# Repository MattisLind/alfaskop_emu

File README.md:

# Alfaskop project

This project aims to make a Alfaskop 4110 running towards the Hercules IBM mainframe emulator and run the Memo mail software by [Verimation](http://www.verimation.se/).

## Alfaskop

The Alfaskop terminal was a big success for the early Swedish IT industry. The product was originally developed by SRT, Standard Radio & Telefon AB which was an ITT owned company. Later the Alfaskop part was moved in to the partly state owned Stansaab. Which then became DataSAAB. DataSAAB was bought by Ericsson to be part of the EIS business unit. Later on when Ericsson concetrated resources on telecom the EIS unit was sold to Nokia. Eventually Nokia part became ICL and the terminal division ended up in terminal manufacturer Wyse Technologies. 

In total 900 000 units were delivered world wide.
More information about the Alfaskop Series 41, marketing material and technical documents can be found [here.](http://www.datormuseum.se/peripherals/terminals/alfaskop). The development of the Alfaskop series of terminals started in the late 1960ies. The first displays, 3100, emulated the IBM 2260 series of terminals. Later models 3500 and 3700 emulated the IBM 3275 and IBM 3277 terminals. S/41 (4100) series emulated te IBM 3278 and IBM 3279 terminals. The S/41 series evolved in into the S/91 seires, with similar capabilities as the S/41 but in more modern hardware.

## Memo mail

The Memo software was originally developed by Volvo IT in the late 1970ies. At its [peak in 1992 over 800](https://sv.wikipedia.org/wiki/Memo_Mail) of the largest coporations in the world used Memo Mail. Memo mail is still developed and maintained by [Verimation AB](http://www.verimation.se/). A [text](https://www.diva-portal.org/smash/get/diva2:80406/FULLTEXT01.pdf) on Memo mail and other early mail systems developed.

## Hercules

The [Hercules](http://www.hercules-390.org/) project aims at emulating the IBM mainframes with its roots in the IBM S/360 architecture. This architecture has seens extensive development since the mid 1960ies when it was introduced. First by the S/370 series and then onto today with the z-series.

## Why
There are today not one single Alfaskop Series 41 terminal that is able to run and show what is was like. The root cause
is that the system as a whole was quite complex. The system 41 terminal of Display Unit (DU) requires a communication processor and a floppy drive (FD) to be able to run. It also has no software built in but loads this from the cluster.
Interfacing towards the cluster is quite complex. It uses synchronous communication and requires specialized hardware to communicate. All these factors jointly most likely made most of these units end up in the trash rather than saved.

Since the system has had an important role in the Swedish IT industry it would be very intersting to show how this system could operate in reality. We wanted to preserve an operating ALfaskop system and demonstrate it operating with as high fidelity as possible.

## Architecture

The above picture show the overall system architecture. It involves tha full Alfaskop cluster with floppy unit and cluster controller together with the terminal itself. The cluster connects using synchronous BSC communication. A small STM32 microcontroller takes care of the BSC protocol. It handles the byte synchronization and the CRC generation and checking. The data is then sent over a ordinary asnynchronous serial line to the Raspberyy Pi serial port. Inside the Raspberry Pi the socat software takes the data from the serial ports and redirects it to the BSC/TCP port of Hercules. Inside Hercules there is an emulation for the IBM 2703 communication unit. The 2703 is controlled by the TCAM software of the MVS operating system. On top of TCAM the TSO, Time Sharing Option, is running which allow users to log in to the system.

## 3270 Data Stream and IBM BSC protocol

The Alfaskop terminals were mostly used for emulating the IBM 3270 terminal series. Although other emulations were available. The software provided from DDHF is the 3270 BSC variant. The 3270 data stream is described in [this](http://bitsavers.trailing-edge.com/pdf/ibm/3270/GA23-0059-4_3270_Data_Stream_Programmers_Reference_Dec88.pdf) document. The [documentatation](http://bitsavers.org/pdf/ibm/3274/GA23-0061-1_3274_Control_Unit_Description_and_Programmers_Guide_Jan84.pdf) for the IBM 3274 Control Unit provide relevant information on how the communication towards the host takes place. The communicationprocessor could either be connected locally to the IBM main frame or remotely using a dial-up or leased line. In the host end there is a [2703](http://bitsavers.informatik.uni-stuttgart.de/pdf/ibm/2703/GA27-2703-1_2703_Transmission_Ctl_Component_Descr_May67.pdf) or [3704](http://bitsavers.informatik.uni-stuttgart.de/pdf/ibm/3704_3705/GC30-3004-5_3704_3705_Communications_Controller_Principles_of_Operation_May1979.pdf) or similar IBM communication unit that interfaces towards the IBM processor. The line normally used 9600 bps syncrounous BSC communication described in [this](http://bitsavers.trailing-edge.com/pdf/ibm/datacomm/GA27-3004-2_General_Information_Binary_Synchronous_Communications_Oct70.pdf) document.

## Alfaskop software

The Alfaskop Series 41 was primarily used as a terminal with emulating various terminal types, like IBM 3278, UNIVAC UTS 400, DEC VT100 etc. The Alfaskop series of terminals were programmed in a special language, SPL. From the beginning this meant StanSAAB Programming Language and was a modified variant of PL/1 programming language. The SPL programming language was developed in PL/1 on a IBM mainframe by a consultant that worked for Stansaab as an under consultant for Programmator around 1977-1978. He worked closely with the person developing the operating system. The operating system was coded entirely in 6800 assembler. The SPL programming language allowed inline assembler constructs if the software developer wanted to improve performance and the compiler has mechanims to do optimizations on the global level.

Later on other software was developed for the Alfaskop series 41, like Alfaword, which was a wordprocessing package.  Another package was called Alfaform. These software packages were also coded in the SPL programming language. There was also a port of the UCSD p-system to the System 41 series. Together with FD4120 floppy drive a complete personal computer was formed. The only software found this far is the 3278 terminal emulation software to be used in the clustered configuraration (4016). Unfortunately very little software for the Alfaskop system has been preserved. If you happen to have any software for the Alfaskop series, please get in contact with me. 

The system software diskette 4016 has been found at Dansk Datahistorisk Förening. This disk has origninally been with SAS. People at DDHF made an image dump of this disk and provided it to us.

## Old architecture idea

In the beginning of this project we had no access to a CPR4101 neither a FD4120 unit. The initial idea was that based on the software  and the scematics that was available an emulation of the floppy unit and cluster controller could be developed in the MAME framework. It turned out to be quite complicated and is still unfinished. The lack of specification of the programmable logic parts turned out to be a major problem since large part of the interrupt handling was taking place in them. When we eventually were able to get our hands on the real units the focus shited to get the full system running and not emulating parts of the cluster. Thus this the old architecture that was envisioned.

The basic idea is to use MAME to emulate the CP and the FD. All technical documentation and schematics are available and is scanned.

To communicate between the various entities of the cluster a TCP variant of the two wire bus will be created eumlating the 32 ports of the CP. To interface to the real Alfaskop DU 4110 a two-wire bus to TCP bridge will be created. In the first implementation it will use an Ericsson TWIB PC board connected to a small uController and a ESP32. Later on the interfacing will be done using a CPLD connected to a ESP32. The CPLD will handle HDLC and include the MODEM.

## Interfacing with SS3

The special twinax connnector used for the Alfaskop series was devolped by Ossi Carlsson AB, an ELDON AB company. The bus called SS3 which employed a 9.585 MHz (half the pixel clock of the terminal) clock to recover the approximately 300 kbit/s signal modulated by FFSK. The signalling over the link employed HDLC. Initially the FFSK modem was implemented using discrete TTL circuits and a bipolar PROM. Later on a Ferranti ULA (custom IC) was designed which did the entire modulation and demodulation process. 

In an attempt to interface to the SS3 bus the easiest was to actually reuse one of the Ericsson made TWIB PC-bus boards that happened to be available. The board is very simple and has just the Intel 8274 HDLC chip and some adress decoding as well as DMA and interrupt logic. Apart for that there is also a twin wire MODEM circuitry including the Ferranti ULA.

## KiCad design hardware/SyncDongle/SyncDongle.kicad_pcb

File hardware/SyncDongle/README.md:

# SyncDongle

SyncDongle is a STM32F103 BluePill or STM32F4x1 Weact blackpill board that interfaces to a sync port. It has the STM32 CPU card and a couple of MAX208 RS-232 level converters, a DB25 connector, a DE9 connector and 10 pin DIP switch / wire wrap area to set various configurations of the serial port. At this point the firmware available only support the STM32F103 BluePill. Support for the Weact black pill will be added later on.

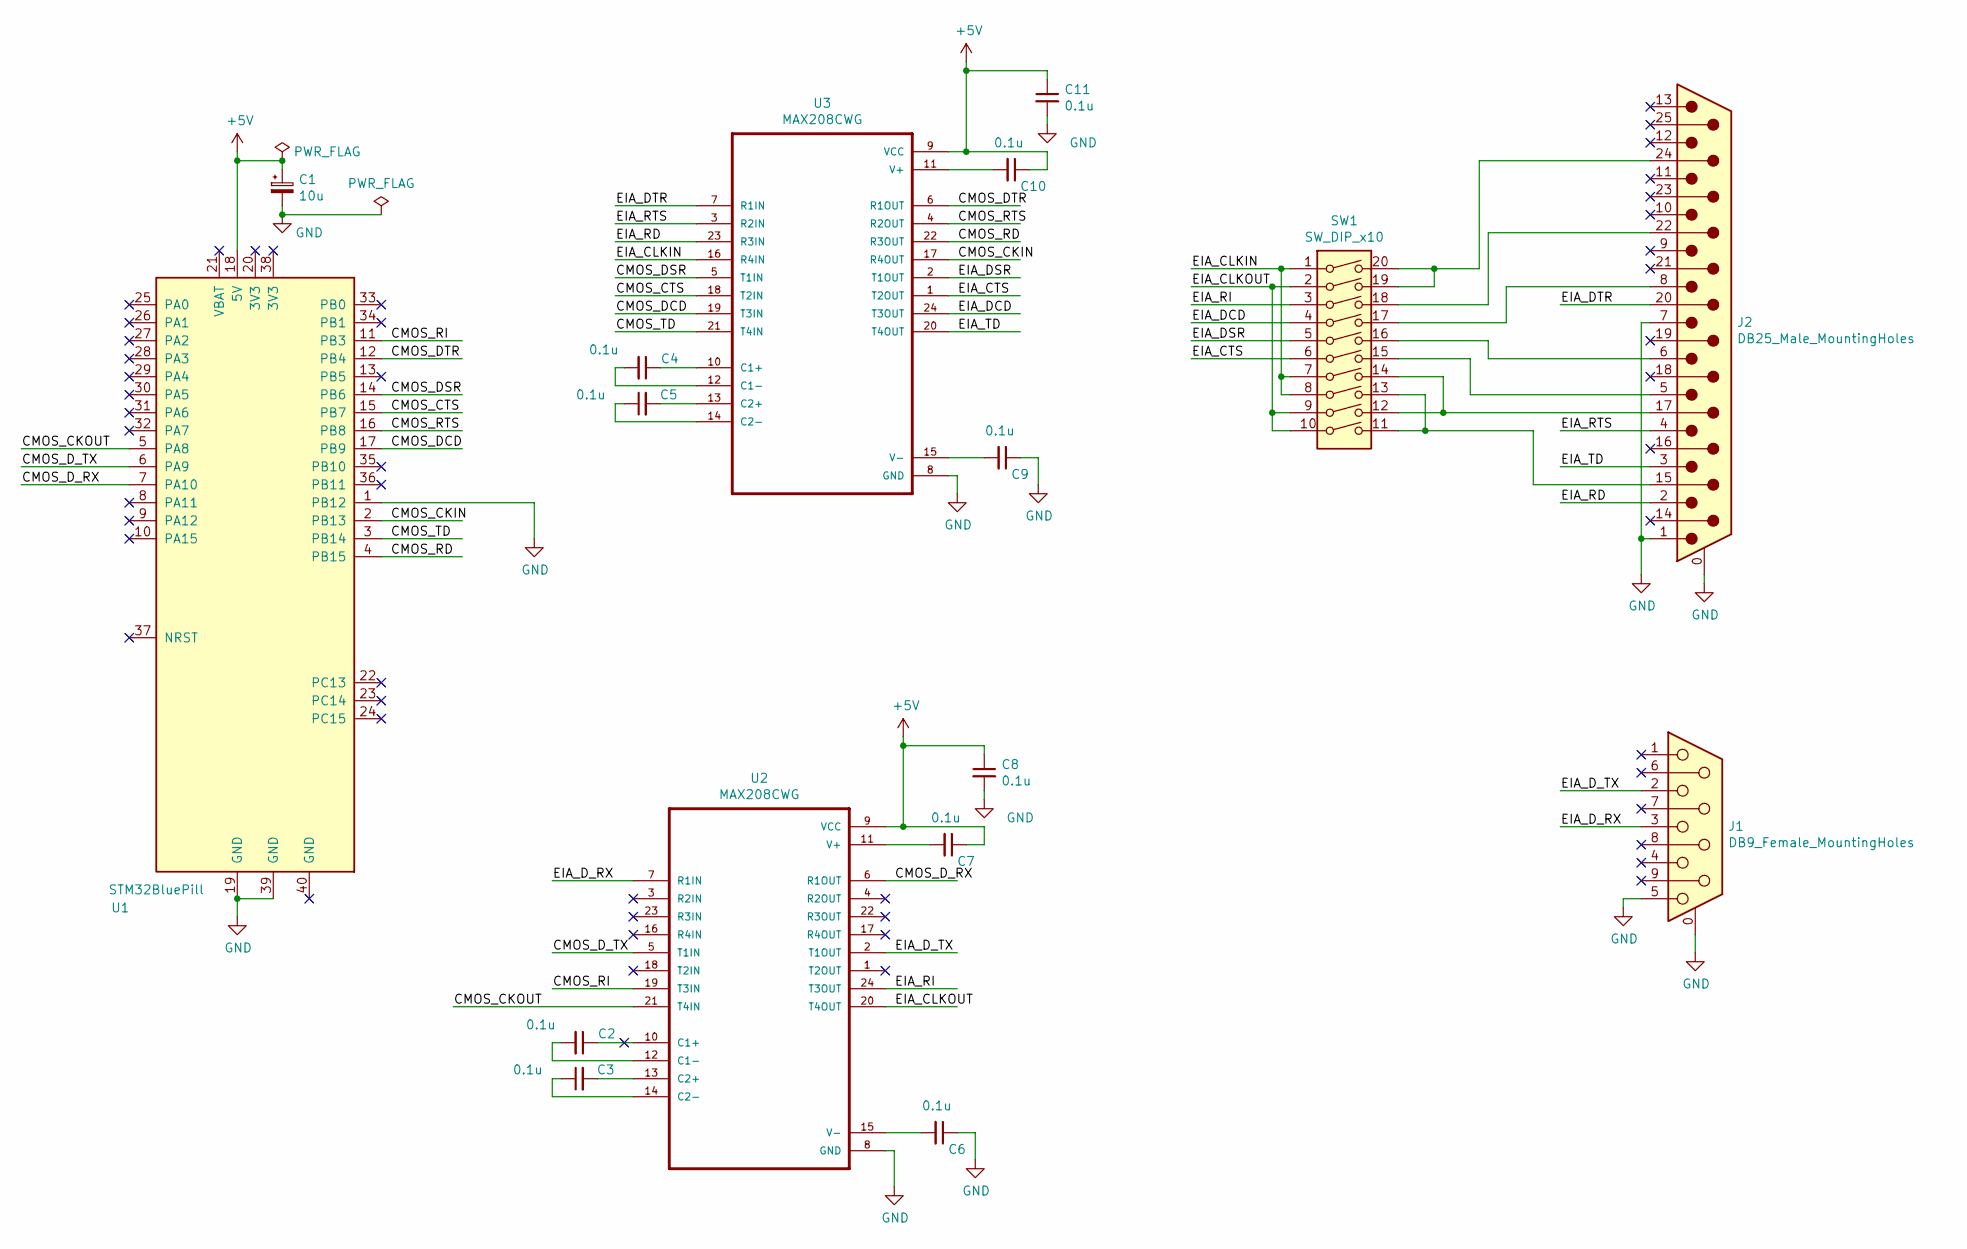
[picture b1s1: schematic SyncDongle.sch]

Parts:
C1: 10u; CP_Radial_D5.0mm_P2.00mm
C2, C3, C4, C5, C6, C7, C8, C9, C10, C11: 0.1u
J1: DB9_Female_MountingHoles
J2: DB25_Male_MountingHoles
SW1: SW_DIP_x10; DIP-20_W7.62mm_LongPads
U1: STM32BluePill; DIP-40_W15.24mm
U2, U3: MAX208CWG; DIP-24_W7.62mm_LongPads

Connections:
+5V: C1.1, C7.1, C8.1, C10.1, C11.1, U1.18 (5V), U2.9 (VCC), U3.9 (VCC)
/CMOS_CKIN: U1.2 (PB13), U3.17 (R4OUT)
/CMOS_CKOUT: U1.5 (PA8), U2.21 (T4IN)
/CMOS_CTS: U1.15 (PB7), U3.18 (T2IN)
/CMOS_DCD: U1.17 (PB9), U3.19 (T3IN)
/CMOS_DSR: U1.14 (PB6), U3.5 (T1IN)
/CMOS_DTR: U1.12 (PB4), U3.6 (R1OUT)
/CMOS_D_RX: U1.7 (PA10), U2.6 (R1OUT)
/CMOS_D_TX: U1.6 (PA9), U2.5 (T1IN)
/CMOS_RD: U1.4 (PB15), U3.22 (R3OUT)
/CMOS_RI: U1.11 (PB3), U2.19 (T3IN)
/CMOS_RTS: U1.16 (PB8), U3.4 (R2OUT)
/CMOS_TD: U1.3 (PB14), U3.21 (T4IN)
/EIA_CLKIN: SW1.1, SW1.7, SW1.8, U3.16 (R4IN)
/EIA_CLKOUT: SW1.2, SW1.9, SW1.10, U2.20 (T4OUT)
/EIA_CTS: SW1.6, U3.1 (T2OUT)
/EIA_DCD: SW1.4, U3.24 (T3OUT)
/EIA_DSR: SW1.5, U3.2 (T1OUT)
/EIA_DTR: J2.20, U3.7 (R1IN)
/EIA_D_RX: J1.3, U2.7 (R1IN)
/EIA_D_TX: J1.2, U2.2 (T1OUT)
/EIA_RD: J2.2, U3.23 (R3IN)
/EIA_RI: SW1.3, U2.24 (T3OUT)
/EIA_RTS: J2.4, U3.3 (R2IN)
/EIA_TD: J2.3, U3.20 (T4OUT)
GND: C1.2, C6.1, C8.2, C9.1, C11.2, J1.0 (PAD), J1.5, J2.0 (PAD), J2.1, J2.7, U1.1 (PB12), U1.19 (GND), U1.39 (GND), U2.8 (GND), U3.8 (GND)
unnamed: C2.1, U2.10 (C1+)
unnamed: C2.2, U2.12 (C1-)
unnamed: C3.1, U2.14 (C2-)
unnamed: C3.2, U2.13 (C2+)
unnamed: C4.1, U3.10 (C1+)
unnamed: C4.2, U3.12 (C1-)
unnamed: C5.1, U3.14 (C2-)
unnamed: C5.2, U3.13 (C2+)
unnamed: C6.2, U2.15 (V-)
unnamed: C7.2, U2.11 (V+)
unnamed: C9.2, U3.15 (V-)
unnamed: C10.2, U3.11 (V+)
unnamed: J2.5, SW1.15
unnamed: J2.6, SW1.16
unnamed: J2.8, SW1.17
unnamed: J2.15, SW1.11, SW1.13
unnamed: J2.17, SW1.12, SW1.14
unnamed: J2.22, SW1.18
unnamed: J2.24, SW1.19, SW1.20

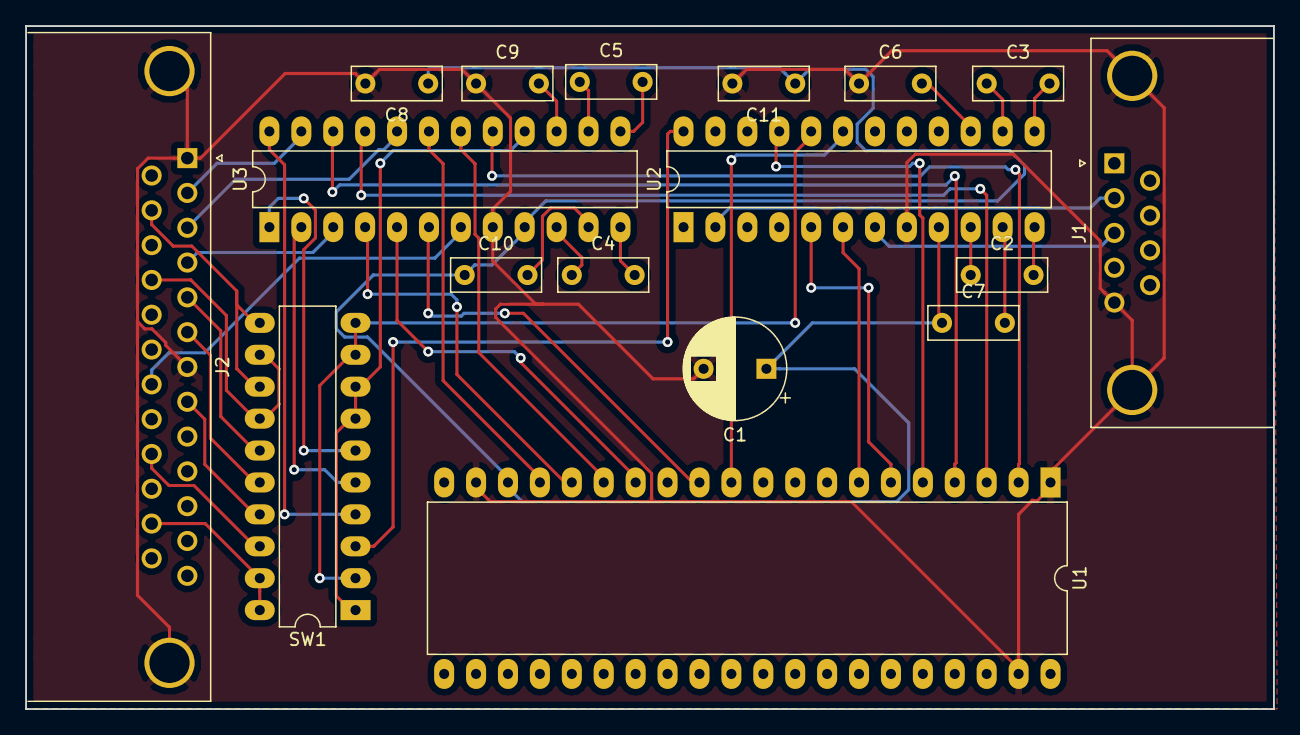
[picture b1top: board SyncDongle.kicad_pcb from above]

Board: 2 copper layers, 99.3 x 54.4 mm, 17 parts (0 on the bottom side), 45 nets.

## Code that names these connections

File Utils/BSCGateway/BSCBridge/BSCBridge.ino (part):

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#include "SyncFSM.h"
#include "MessageFSM.h"
#define DEBUG_LEVEL 0 
#define RTS PB8 // Input
#define RFS PB7  // Output CTS
#define DTR PB4  // Input
#define RI PB3   // Output
#define DSR PB6  // Output
#define DCD PB9  // Output 
#define ACTIVITY PC13 // Activity LED

#define HostSerial Serial
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

HardwareTimer pwmtimer(1);
const int pwmOutPin = PA8; // pin10

class RingBuffer rxBuffer;
class RingBuffer txBuffer;
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
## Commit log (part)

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2019-12-22 Added PROMN to readme
2019-12-22 Renamed file
2019-12-22 Added pics
2019-12-29 Added pictures of the cable between SCA card and panel
2019-12-29 Started adding info on the SCA cable
2020-01-09 Added picture when running the terminal
2020-01-13 Added a header for ebcdic codes
2020-01-13 Added a crc-16 algorithm as well PAD character to the ebcdic file@
2020-01-13 Added utils for BSC testing with 8274 and SPI
2020-01-14 Included ebcdic.h header file.
2020-01-14 Added basic state machine
2020-01-14 Implemented first try of a receive state machine.
2020-01-15 Debugging needed..
2020-01-15 Yet more debugging
2020-01-16 Added a LSB to MSB translation array
2020-01-16 Used MSBFIRST with mapping table is the solution.
2020-01-16 Now able to find sync correctly and receive ENQ message
2020-01-17 A lot of editing going on.
2020-01-17 initial fixing of code. WIP
2020-01-18 Added a test case and fixed the SyncFSM code
2020-01-18 Added an embryo to test case and code for the MessageFSM
2020-01-18 Now EOT test passes!
2020-01-19 Added NAK test
2020-01-19 Added ACK0 test
2020-01-19 Added ACK1 test passes
2020-01-19 Added WACK test passes
2020-01-19 Status message test passes
2020-01-19 Test message test passes
2020-01-19 Text message test passes
2020-01-20 Added info on interface signal handling.
2020-01-20 Move around files a bit
2020-01-20 Skeleton for ESP32 part with provisions to run it udner Linux
2020-01-21 Changes needed due to moving files.
2020-01-22 Fixes to wrapper code
2020-01-22 Added a heler header file
2020-01-23 Moved files
2020-01-23 Separated out Serial.cpp to make it available for other projects more easily
2020-01-23 Starting to do a combined test with all STM32 modules involved including the .ino file
2020-01-23 Fixes to get it running echoin characters.
2020-01-23 First commit of CombinedTest and Arduino dummy wrapping code
2020-01-23 fixes
2020-01-24 Forgot this file...
2020-01-24 Fixes to at least make the combined test compile.
2020-01-24 All methods stubbed
2020-01-24 Added two pcap files
2020-01-24 Added two Wireshark pictures
2020-01-24 fixed sketch
2020-01-25 Added more complete code. Compiles and links
2020-01-25 Added .gitignore file
2020-01-25 Added a CommandSerializer class to handle serial comm in both ends
2020-01-25 Starting fixing test cases for CommandSerializer class
2020-01-25 Fixed a number of test cases
2020-01-25 Added P and S test cases
2020-01-26 Added all test cases. No moreIsComming need testing.
2020-01-27 Added tests of crc algo used. Do they match crc reveng?
2020-01-28 Added crc for test message
2020-01-28 Fixed CRC checking
2020-01-28 WIP: Protocol state machine
2020-01-30 Introduced a substate to handle the rts/cts handshake .
2020-01-30 Started creating tests for ProtocolFSM
2020-01-30 Test case poll WIP
2020-01-31 Clang complained about some things that GCC didn't bother about
2020-01-31 Fixed first POLL test sequence
2020-01-31 Started working on write test case
2020-02-03 Begin looking at transparent mode and multi message blocks for write
2020-02-03 WIP Write command
2020-02-05 Write WIP
2020-02-05 First Write test case done
2020-02-05 Refactor test and added verification of received message
2020-02-06 Added a macro to verify the RTStransaction
2020-02-06 Cleand up POLL test case.
2020-02-07 Cleaned up test cases. Now POLL
2020-02-10 Need to check the callback as well
2020-02-10 callback impl.
2020-02-11 Now verifying the response from the protocol stack.
2020-05-19 Add work on Hercules Integration
2020-05-19 First update
2020-05-19 small changes
2020-05-19 Added JCL and conf files to create TCAM for R3270
2020-05-20 WIP: connect to Hercules over BSC test tool.
2020-05-20 Added a TCAM support picture
2020-05-20 Made the herculesConnect program to compile correctly.
2020-05-20 Tested - now it does poll OK. But Hercules closes down in a bad way.
2020-05-23 Added a pciture and fixed some test code
2020-05-23 Added picture
2020-05-23 Added the schematic as a picture
2020-05-23 Added 3274 emu project and some changes to the BSCGatway sketch
2020-05-24 Added stolen skeleton code for my experiment.
2020-05-24 Renamed file into .cpp since we are hoping to use c++.
2020-05-24 Oops. Wrong file name.
2020-05-24 Now compiles.
2020-05-24 Able to send preformatted dump taken from Wireshark. Displayed OK. Recived AID 7d when pressing ENTER on logon prompt as expected
2020-05-25 More testing of 3274emu.
2020-05-25 Now able to log in
2020-05-25 Added TSO login pictures
2020-05-25 Update with pictures of successful login
2020-05-26 logging to a separate log file
2020-05-26 Increased buffer size drastically
2020-05-26 Changes to bigger buffer and fixed logging.
2020-05-27 Not sending neither anticipating CRC bytes in Hercules mode.
2020-05-28 Added screen dumps
2020-06-02 Added a picture of the new architecture.
2020-06-02 Added Memo logo
2020-06-02 Hercules and IBM logo
2020-06-04 Refactor to use a modifier on the constructor to select hercules or non hercules mode.
2020-06-07 Added info on the SPL language.
2020-06-10 Added more links
2020-06-10 Added link to Kaptronix document
2020-06-10 Changed Matt
2020-06-15 Update on VTAM.
2020-06-15 Fleshed out the SDLC part a bit.
2020-06-15 Added a trace
2020-06-16 Added info on RTT.\
2020-06-17 Added link to NCP gen.
2020-06-17 Some old changes that had been lying around
2020-06-17 Fixes for BSCBridge
2020-06-17 The new project for interfacing with Hercules is called BSCBridge
2020-06-17 fixed interconnect between messageFMSs.
2020-06-18 Now with logging
2020-06-18 Now it works looping,
2020-06-21 Indentation fixes.
2020-06-21 Fixed some simple handling for text mode vs control mode.
2020-06-22 Added skeleton based on the BSCBridge program.
2020-06-22 Added some code and thoughts.
2020-06-22 Added info on SDLC sending.
2020-06-22 Now most parts of the sender is probably there.
2020-06-22 Compiles with base testing skeleton
2020-06-23 Added two new classes to handle testing.
2020-06-23 Debugging.
2020-06-23 Removed checksum because it isn't working and fixed bugs
2020-06-24 LSB first.
2020-06-24 Discussion on RX as well.
2020-06-24 Added one step in the list of steps to do.
2020-06-25 Added untested code for rx.
2020-06-26 Fixed spelling!
2020-06-27 Found small bugs
2020-06-28 First attempt to do a test for BSCBridge.
2020-06-29 Try to enable SPI interrupts
2020-06-29 Yet one more paranthesis missing
2020-06-29 Forgot to clear bufferCnt for ENQ.
2020-06-29 Just one rxBuffer
2020-06-29 Fixed logging using three macros - a bit cleaner code.
2020-06-29 Interrupt based SPI variant is working
2020-06-29 One missing paranthesis...
2020-06-29 Some initial testing.
2020-06-29 Refactor and add several test cases.
2020-06-29 BSC test program fixed and tests are passing.
2020-06-29 Added a socat command that works.
2020-06-30 Fix for rxOneCounter to not wrap.
2020-07-01 Picked old stuff to create a test bench for SDLC
2020-07-01 Debugging ...
2020-07-02 bug in escape handling state machine.
2020-07-02 Yet more debugging. Now it transfers ok. But CRC is weird.
2020-07-02 Fixed stuffing code that was wrong and fixed order of CRC. Now passes three tests
2020-07-03 Removed debug printfs from sketch
2020-07-03 Added a test for looping the SDLC interface.
2020-07-03 Better logging. Switched to LSBFIRST.
2020-07-04 Additional logging
2020-07-04 Moved init code and added reset sequence.
2020-07-04 Added flush and close. Now the USB serial behaves better.
2020-07-04 Added separate reset as it appears that the USB serial sends crap when rebooting.
2020-07-04 Changed test to iuse single byte buffer instead of RingBuffer class.
2020-07-04 Converted SDLC code to interrupt based. Updated test case.
2020-07-04 Two tests in a row test...
2020-07-04 Handling Idle flags and reinit when receiving abort.
2020-07-04 Now refactor to work as a SDLC tester.
2020-07-05 Fixed code so that it communicates with real 8274 chip. crc remains unresolved.
2020-07-05 Discussion on crc
2020-07-05 Added more cases to check CRC.
2020-07-06 Yet more fixes for CRC handling. Now it seems to comply with SDLC CRC.
2020-07-06 Add debugging.
2020-07-06 Added text on work with TWIB board to check the code.
2020-07-06 SOme testing of various CRC values
2020-07-06 Fixed logging and the CRC check in transmit path. OK in test case.
2020-07-06 Debug 0. ANd fix for 8274 tester
2020-07-07 Added info on the Informer 213 connector pinout
2020-07-10 Added a todo list.
2020-07-10 Spelling
2020-07-13 Success in communicating with the Informer 213
2020-07-13 Dissecting SNA messages.
2020-07-17 Alfaskop working with BSC
2020-07-17 Fixes for updated MessageFSM module.
2020-07-17 Added CU/DV address in first text response.
2020-07-18 Log cleanup
2020-07-18 Testing supressing ACK if there were an immediate EOT. Maybe not very good. Saved for testing purposes.
2020-07-20 Added section on the Hercules bug.
2020-07-20 Now using USB for host port and serial for debugging
2020-07-22 Testing
2020-07-22 Started developing a PCB dor SyncDongle.
2020-07-22 Added MAX208 libraries
2020-07-22 Added MAX208
2020-07-22 Dip switch 6
2020-07-22 Schematic almost ready.
2020-07-23 Fixed layout.
2020-08-01 Picture of finished PCB
2020-08-03 Changed picture
2020-08-03 Updated text
2020-08-03 SyncDongle update.
2020-08-03 Starting with the socat replacement.
2020-08-04 WIP.
2020-08-05 Now at least compiles...
2020-08-05 Bugfixes. Seems to work. More testing needed though.
2020-08-05 Bugfixes.
2020-08-05 Added a server mode. Not tested yet...
2020-08-08 Use char instead of int and set 4096 byte size.
2020-08-08 Now the rx interrupt put data into buffer rather than do all the processing.
2020-08-08 Refactor the TX of BSC to include a FSM that is polled when there is space availble in buffer.
2020-08-08 More logging in socatReplace.
2020-08-08 Adapted testcase to new txPoll. Fixed bugs. Now passing.
2020-08-08 Now using txPoll
2020-08-12 A line was dropped by mistake.
2020-08-12 Only blue pill supported in the firmware.
2020-08-12 Added instructions on installation of firmware.
2020-08-13 Bugfix for POLL.
2020-08-14 USB port. Link speed 2400 bps.
2020-08-14 Now test is passing.
2020-08-14 Add screen shot of Arduino Env
2020-08-14 Added initial EOT to clear the line.
2020-08-15 BSCBridge testing with 3274emu.
2020-08-16 Added an activit indicator. Use the LED on the Bluepill to signal Rx or Tx activity.
2020-08-16 Using 16 bits SPI transfer size to decrease the amount of interrupts generated.
2020-08-16 Better picture
2020-08-25 Added EOT and NAK. Renamed IUS to ITB.
2020-08-25 Improved error handling.
    Handle cases of unsync when we get link control chars in the non transparent data. Go back to state 0 and try to resync.
2020-08-25 Added textMode control.
2020-08-25 Support for new MessageFSM tx poll API.
2020-08-25 Spelling mistake.
2020-08-29 The IO pins for interface signals had changed from the prototype to the real hardware. Needed fixing!
2022-01-23 Added gerbers.
2022-01-23 Small fixes to 3274_emu that wasn't pushed.
2022-02-21 Added a pdf file of the schematic.
2022-03-07 fixes to make SDLC work and allow for changing baudrate and handshake lines.
2022-03-12 Added more handshake signal controls.
2022-03-19 Disabled generation of CRC as well.
2022-03-19 Restructure code. Added suppport for receiving and sending abort. Removed rxOutBuffer and rxMode concept.
2022-03-19 Make sure an abort is fully received.
2022-03-25 Added description of command protocol.
2022-03-27 Changed buffer code to do unsigned char rather than int and also increased buffer size to 5k to allow up to 8 packets with around 500 bytes eaach.
2022-04-01 Added connector diagram for the DB25 added.
2022-04-01 Added a 8274 data sheet
2022-04-01 Added 8274 data sheet with proper name
2022-04-02 Fix special case when five ones is the last in the frame. Add one extra bit before the flag.
